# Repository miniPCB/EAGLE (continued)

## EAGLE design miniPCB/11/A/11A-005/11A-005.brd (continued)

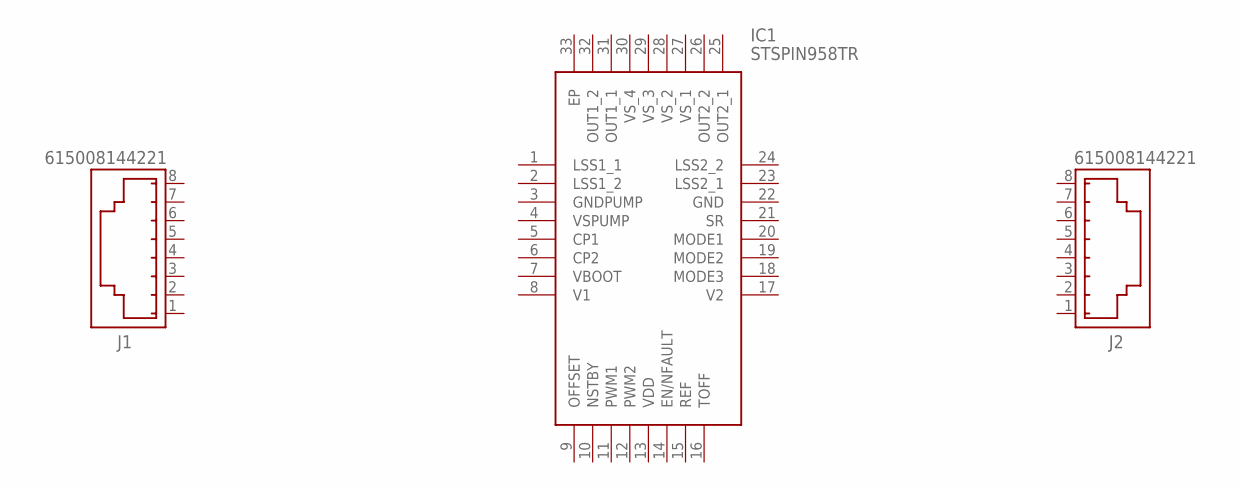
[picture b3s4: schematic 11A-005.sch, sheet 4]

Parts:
IC1: STSPIN958TR; QFN50P500X500X100-33N
J1, J2: 615008144221

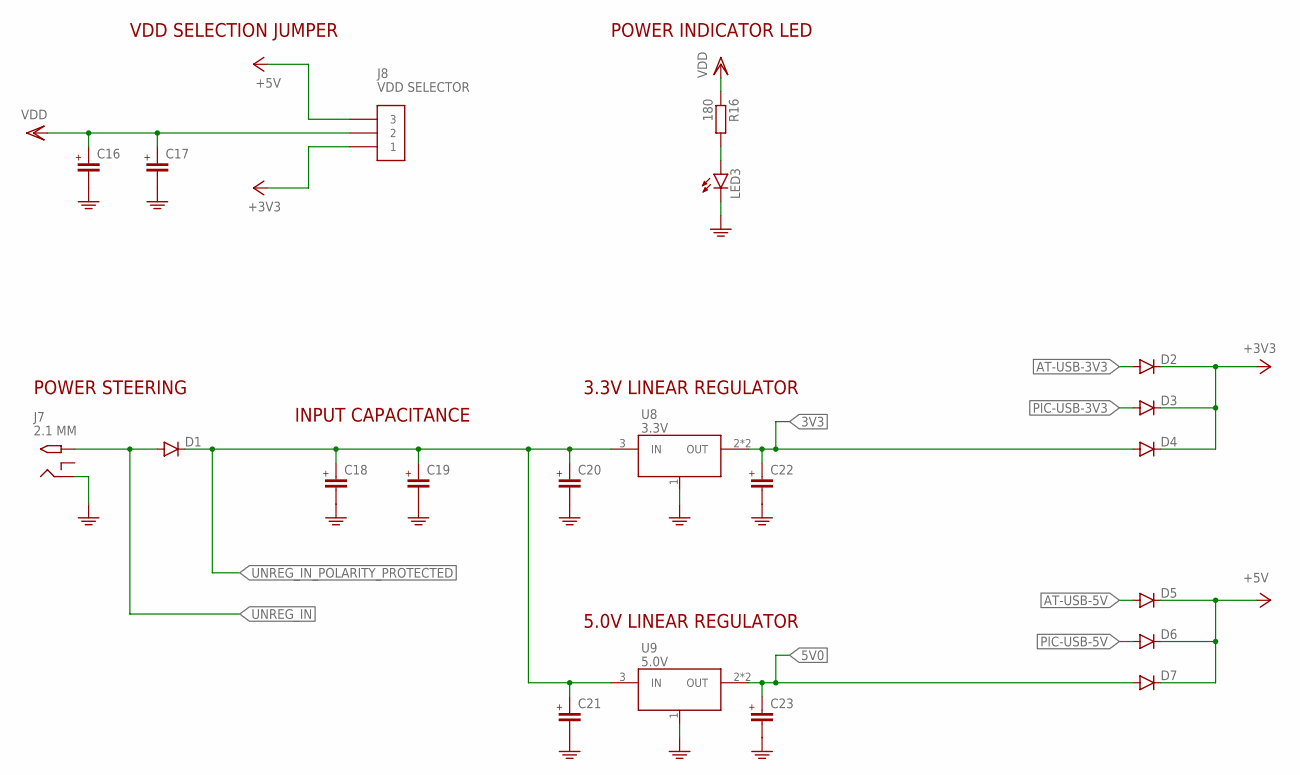
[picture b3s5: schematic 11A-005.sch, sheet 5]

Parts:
C16, C17, C18, C19, C20, C21, C22, C23: C0805
D1, D2, D3, D4, D5, D6, D7: DIODE-DO214AC; DO214AC
J7: 2.1 MM; PJ-102A
J8: VDD SELECTOR; PINS_3
LED3: LEDSML0805; SML0805
R16: 180; R0805
U8: 3.3V; SOT223
U9: 5.0V; SOT223

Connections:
3V3: C22.1 (+), D4.A, U8.2 (OUT), U8.4.TAB (OUT)
5V0: C23.1 (+), D7.A, U9.2 (OUT), U9.4.TAB (OUT)
+3V3: D2.C, D3.C, D4.C, J8.1
+5V: D5.C, D6.C, D7.C, J8.3
AT-USB-3V3: D2.A; also elsewhere on the board
AT-USB-5V: D5.A; also elsewhere on the board
GND: C16.2 (-), C17.2 (-), C18.2 (-), C19.2 (-), C20.2 (-), C21.2 (-), C22.2 (-), C23.2 (-), J7.RING, LED3.C, U8.1 (GND), U9.1 (GND); also elsewhere on the board
LED_POWER: LED3.A, R16.2
PIC-USB-3V3: D3.A
PIC-USB-5V: D6.A
UNREG_IN: D1.A, J7.TIP
UNREG_IN_POLARITY_PROTECTED: C18.1 (+), C19.1 (+), C20.1 (+), C21.1 (+), D1.C, U8.3 (IN), U9.3 (IN)
VDD: C16.1 (+), C17.1 (+), J8.2, R16.1; also elsewhere on the board

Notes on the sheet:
VDD SELECTION JUMPER
POWER INDICATOR LED
3.3V LINEAR REGULATOR
5.0V LINEAR REGULATOR
POWER STEERING
INPUT CAPACITANCE

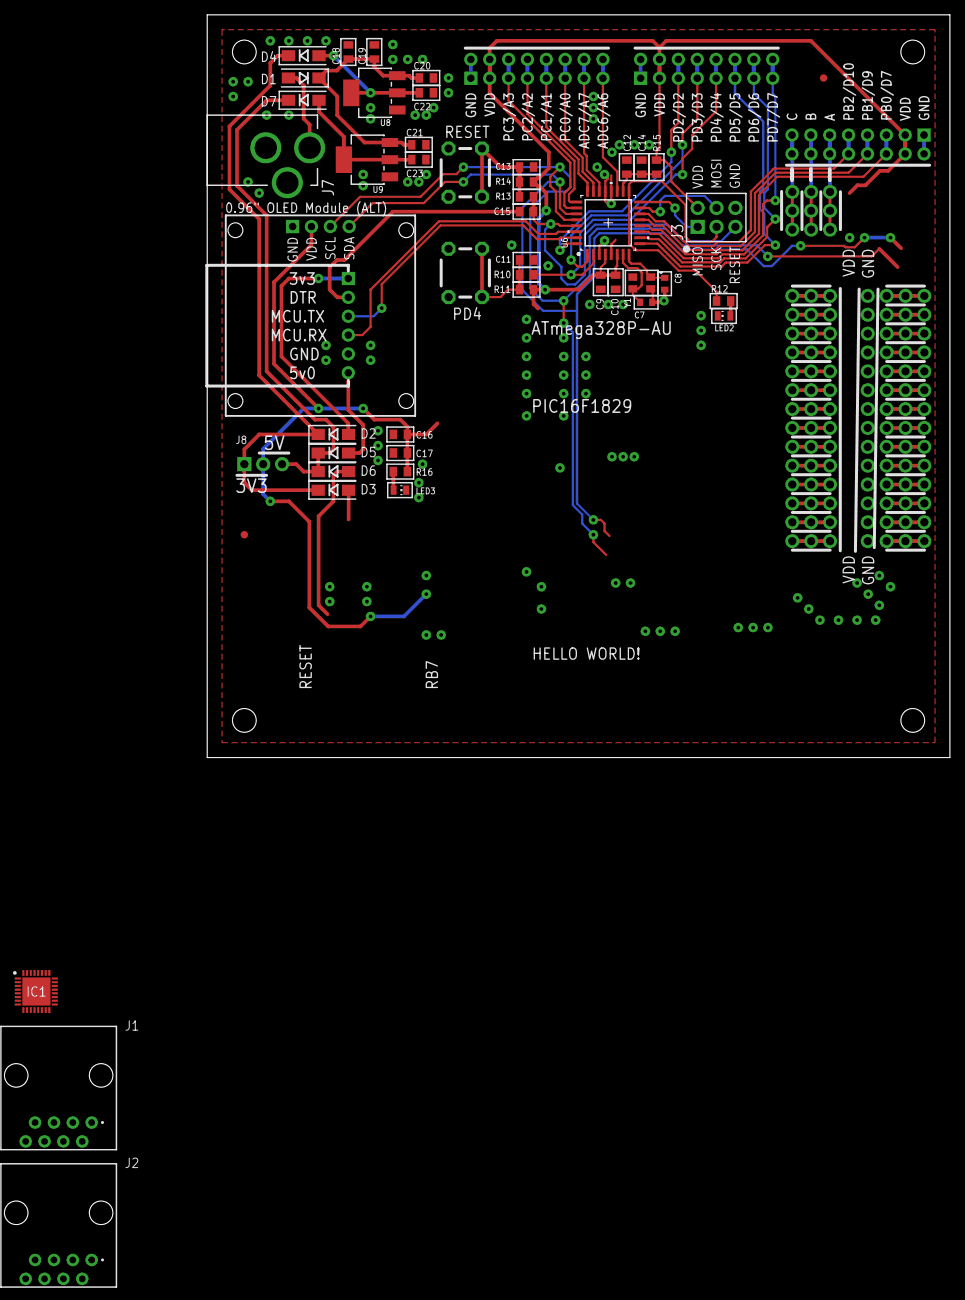
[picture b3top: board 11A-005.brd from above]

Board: 2 copper layers, 100.0 x 100.0 mm, 54 parts (0 on the bottom side), 44 nets.

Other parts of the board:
U$1: MINIPCB_PANEL_IMAGEFRAME

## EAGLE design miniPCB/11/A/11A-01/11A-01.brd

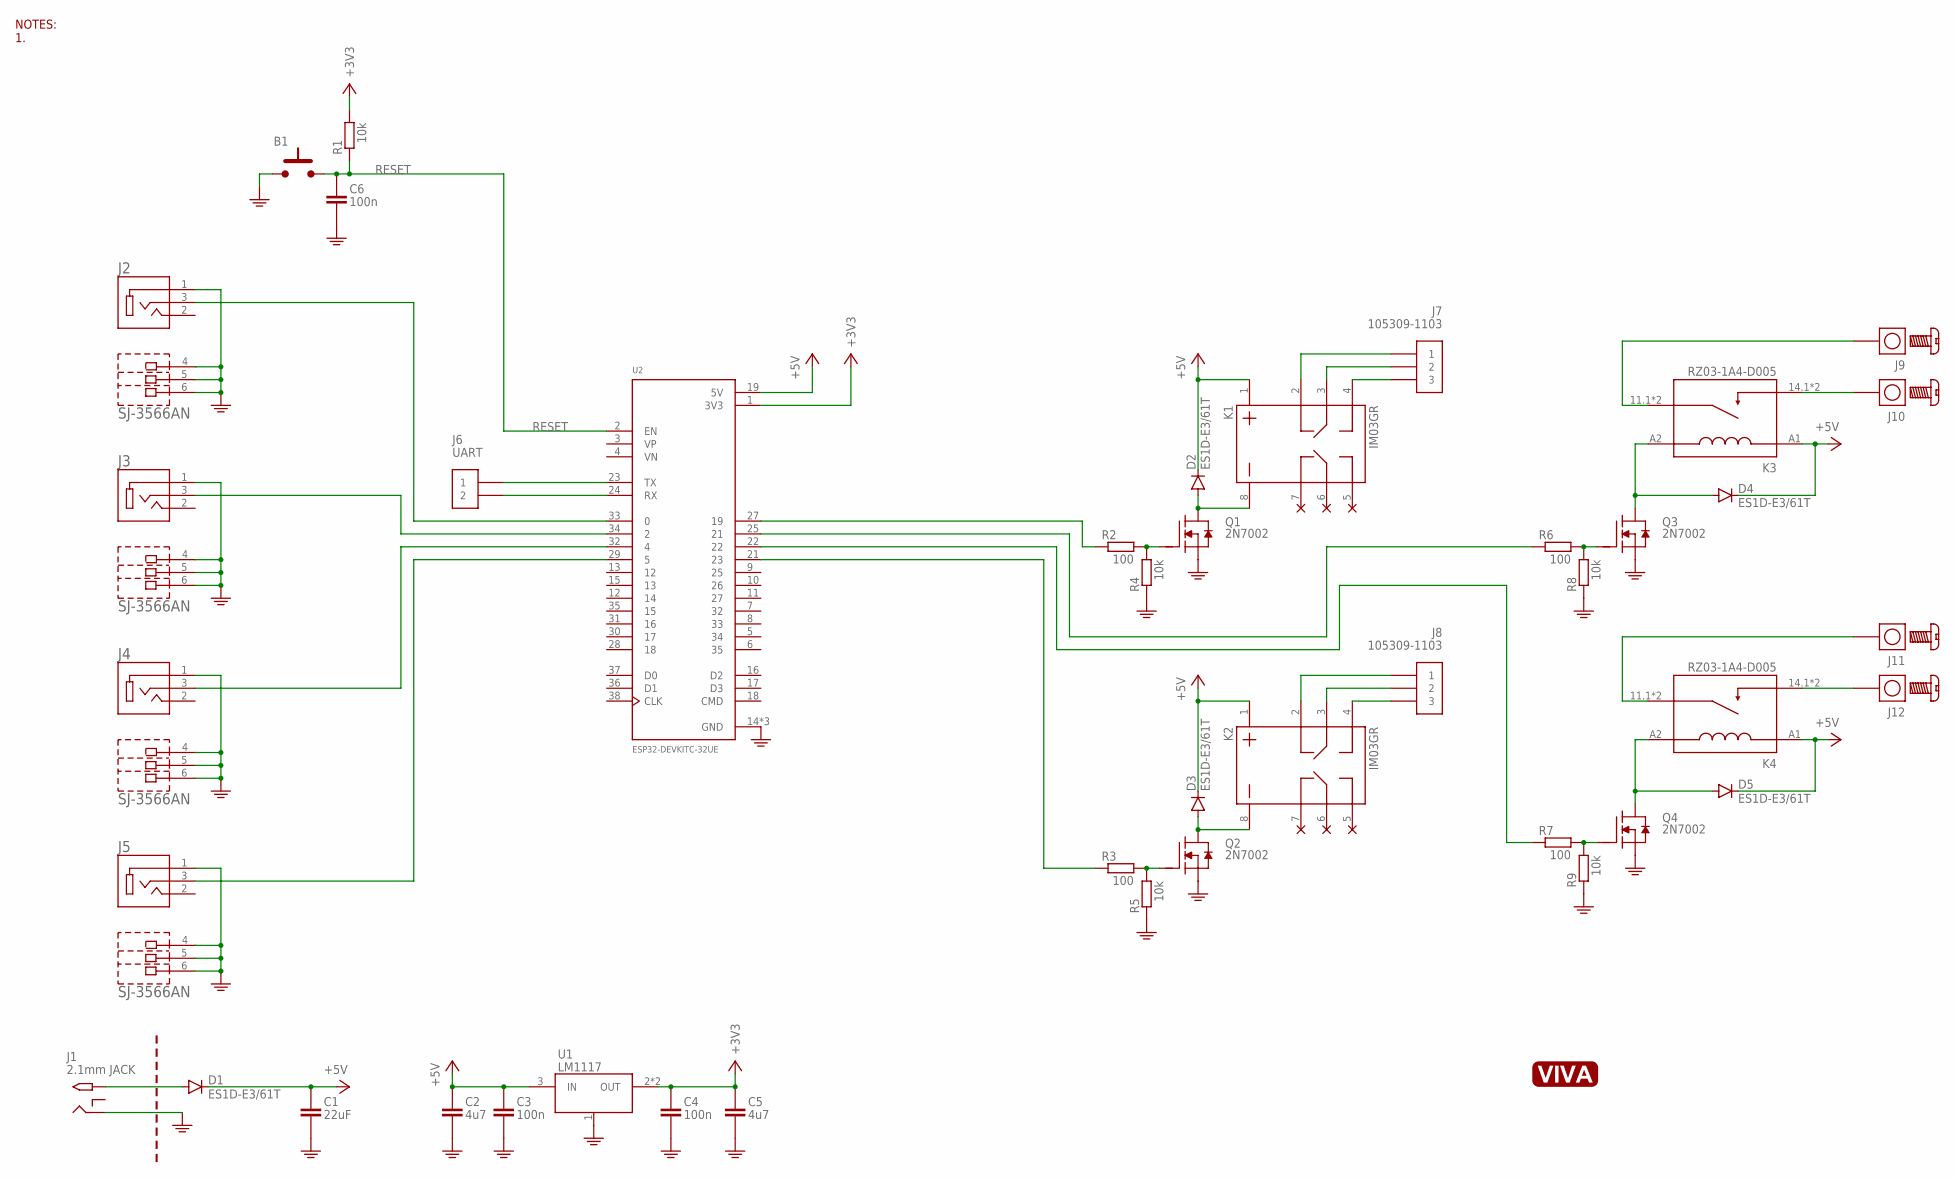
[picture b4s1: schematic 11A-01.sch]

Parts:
B1: PUSHBUTTON6MMSMD; PUSHBUTTON-6MM-SMD
C1: 22uF; C3-5MM
C2, C5: 4u7; C0805
C3, C4, C6: 100n; C0805
D1, D2, D3, D4, D5: ES1D-E3/61T; DO214AC
J1: 2.1mm JACK; PJ-102A
J2, J3, J4, J5: SJ-3566AN; CUI_SJ-3566AN
J6: UART; PINS_2
J7, J8: 105309-1103; PINS_3-NANOFIT
J9, J10, J11, J12: SCREW-TERMINAL; SCREW-TERMINAL-M3
K1, K2: IM03GR; RELAY_IM03GR
K3, K4: RZ03-1A4-D005; RELAY_RZ03-1A4-D005
PCB1: MINIPCB_0P100X100; MINIPCB_DOCK_100X100; PART_NUMBER 11A-01
Q1, Q2, Q3, Q4: 2N7002; SOT23
R1, R4, R5, R8, R9: 10k; R0805
R2, R3, R6, R7: 100; R0805
U1: LM1117; SOT223
U2: ESP32-DEVKITC-32UE; ESPRESSIF_ESP32-DEVKITC-32UE
U$1: VIVA_LOGO

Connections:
3V3: U2.1 (3V3)
5V: U2.19 (5V)
+3V3: C4.1ASD (+), C5.1ASD (+), R1.2, U1.2 (OUT), U1.4.TAB (OUT)
+5V: C1.+, C2.1ASD (+), C3.1ASD (+), D1.C, D2.C, D3.C, D4.C, D5.C, K1.1, K2.1, K3.A1, K4.A1, U1.3 (IN)
GND: B1.1, B1.2 (1), C1.-, C2.2ASDF (-), C3.2ASDF (-), C4.2ASDF (-), C5.2ASDF (-), C6.2ASDF (-), J1.RING, J2.1, J2.5, J2.6, J3.1, J3.5, J3.6, J4.1, J4.5, J4.6, J5.1, J5.5, J5.6, Q1.2 (S), Q2.2 (S), Q3.2 (S), Q4.2 (S), R4.1, R5.1, R8.1, R9.1, U1.1 (GND), U2.14 (GND), U2.20 (GND), U2.26 (GND)
unnamed: Q1.1 (G), R2.2, R4.2
unnamed: D4.A, K3.A2, Q3.3 (D)
unnamed: Q3.1 (G), R6.2, R8.2
unnamed: J10.1, J10.2, J10.3, J10.4, K3.14.1 (14), K3.14.2 (14)
unnamed: J9.1, J9.2, J9.3, J9.4, K3.11.1 (11), K3.11.2 (11)
unnamed: D2.A, K1.8, Q1.3 (D)
unnamed: D5.A, K4.A2, Q4.3 (D)
unnamed: Q4.1 (G), R7.2, R9.2
unnamed: J12.1, J12.2, J12.3, J12.4, K4.14.1 (14), K4.14.2 (14)
unnamed: J11.1, J11.2, J11.3, J11.4, K4.11.1 (11), K4.11.2 (11)
unnamed: J7.3, K1.4
unnamed: J7.2, K1.3
unnamed: J7.1, K1.2
unnamed: Q2.1 (G), R3.2, R5.2
unnamed: D3.A, K2.8, Q2.3 (D)
unnamed: J8.3, K2.4
unnamed: J8.2, K2.3
unnamed: J8.1, K2.2
unnamed: D1.A, J1.TIP
unnamed: J6.1, U2.23 (TX)
unnamed: J6.2, U2.24 (RX)
unnamed: J2.3, U2.33 (0)
unnamed: J3.3, U2.34 (2)
unnamed: J4.3, U2.32 (4)
unnamed: J5.3, U2.29 (5)
unnamed: R2.1, U2.27 (19)
unnamed: R6.1, U2.25 (21)
unnamed: R7.1, U2.22
unnamed: R3.1, U2.21 (23)
RESET: B1.3 (2), B1.4 (2), C6.1ASD (+), R1.1, U2.2 (EN)

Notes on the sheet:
NOTES: 1.

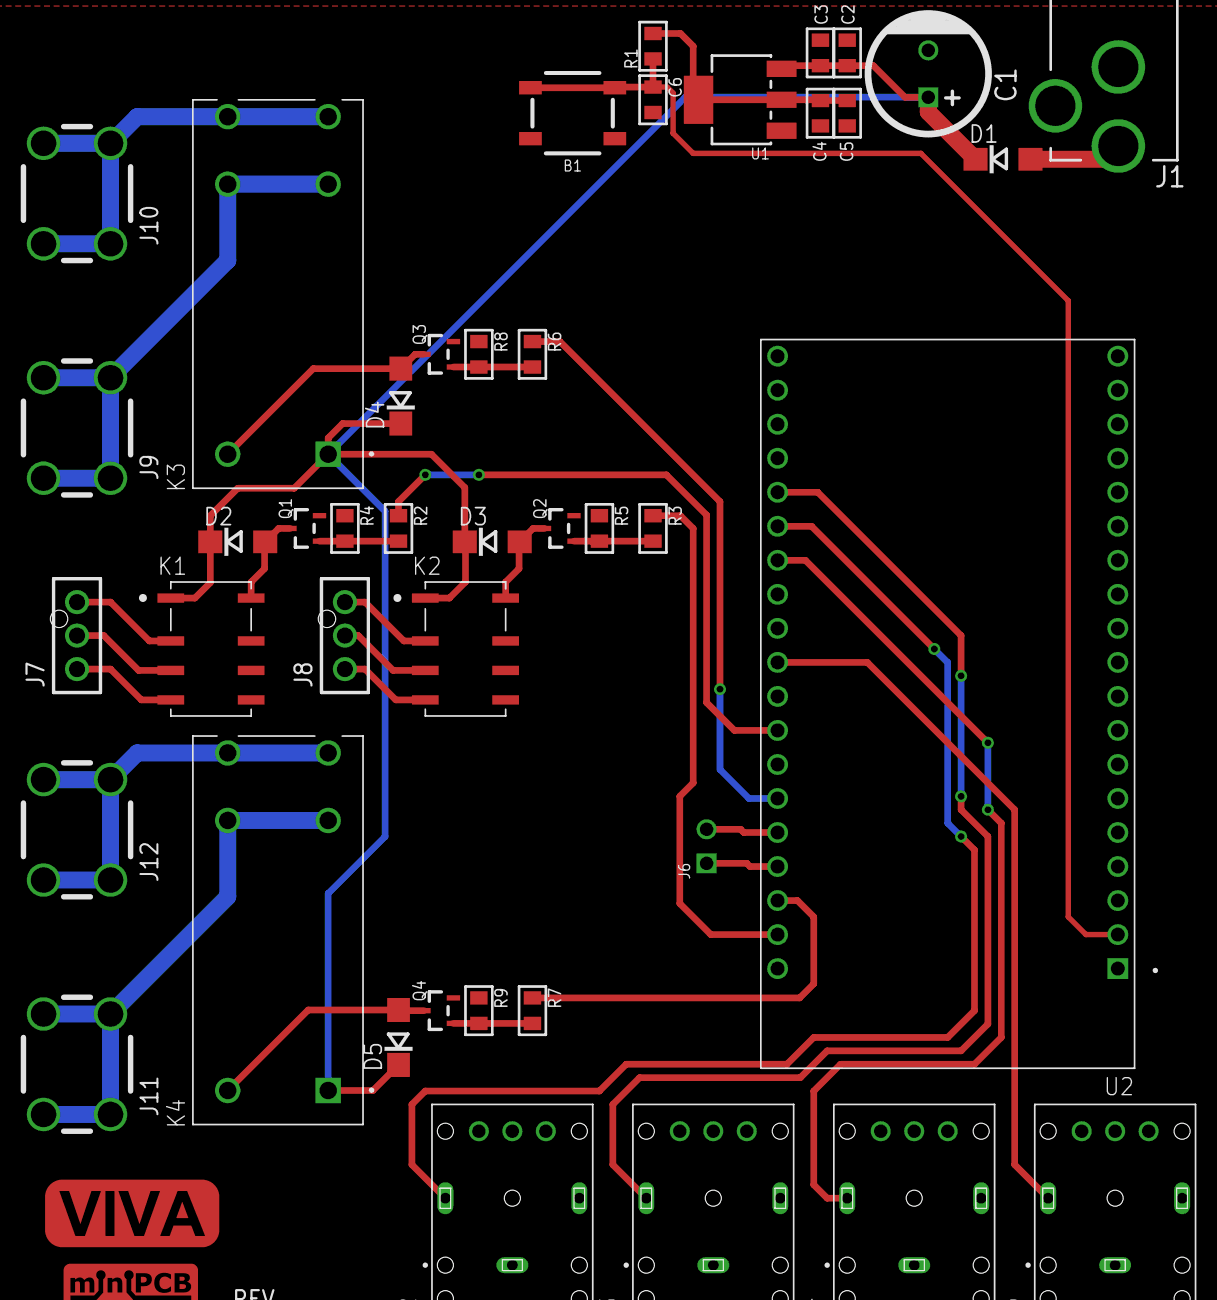
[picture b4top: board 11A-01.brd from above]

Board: 4 copper layers, 45 parts (0 on the bottom side), 33 nets.
